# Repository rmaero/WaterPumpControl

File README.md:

Water Pump Controller
Sistema de control automático para bombas de agua en instalaciones residenciales con cisterna y tanque elevado. Diseñado para optimizar el consumo energético y prevenir funcionamiento en seco de la bomba. La version mas actual del firmware es "MEF_IF_EEPROM".

Video demostracion
https://youtu.be/jwLdcLJ9unM

Sistema en producción implementado desde 2023

Estado: En Producción
Operando continuamente desde 2023 sin fallas en instalación residencial real.
REV. B: corregido invertidos pines Rx y Tx, resistencia pulldown de Q1. Agregado conector J10 para programar bootloader (no implementado todavia).

Problema que Resuelve
En sistemas tradicionales de cisterna + tanque elevado, las bombas funcionan con controles manuales, niveles flotantes o temporizadores simples, lo que genera:

Riesgo de funcionamiento en seco (daño a la bomba) en caso de que un sensor falle.
Desperdicio energético (bomba funcionando innecesariamente)
Falta de monitoreo del estado del sistema

Este controlador automatiza completamente el proceso con lógica inteligente. Brinda testigos luminicos para relevar el estado del tanque y de la cisterna (muy util tambien para verificar si los sensores estan funcionando correctamente en caso de aviso de falla).

Características
Hardware

Diseño de PCB custom con microcontrolador ATmega328.
Sensores de nivel de agua en cisterna y tanque
Relé para control de bomba (220V/15A)
Protección contra funcionamiento en seco
Indicadores LED de estado
Posibilidad de usar la placa como standalone sin microcontrolador integrado, sino conectandolo atraves de pines provistos en el etremo izquierdo. Facilidad para usar un ESP32 por ejemplo.

Firmware

Lógica de histéresis para evitar ciclos cortos
Protección multi-nivel:

Detección de cisterna vacía
Timeout de seguridad

Funcionamiento
Lógica básica:

Sensor detecta nivel bajo en tanque y nivel alto en cisterna → activa bomba
Sensor verifica nivel suficiente en cisterna
Bomba llena tanque hasta nivel alto
Sistema entra en standby hasta próximo ciclo

Proteccion contra funcionamiento en seco:
Por defecto, dado el caso para el que se diseñó este circuito, el tanque tiene una capacidad muy superior a la cisterna y la bomba es capaz de vaciar la cisterna en 2:15 minutos. Por lo cual se implementó un timeout que si a los 3 minutos el sensor de la cisterna no está en bajo, asume que es por falla del sensor, apaga la bomba y se queda en estado de ERROR con led rojo parpadeando

Funcion LEARN:
se puede programar que el sistema aprenda de forma automatica cuanto tiempo demora en vaciarse la cisterna. Para esto se debe tener el tanque completamente vacio y la cisterna completamente llena. Con la placa desenergizada, mantener apretado el pulsador "LEARN" y energizar la placa. Una vez que se haya encendido la bomba se puede soltar el pulsador. En este estado el microcontrolador contará el tiempo que demore en vaciarse la cisterna y lo guardará en memoria no volatil (por lo que se puede reiniciar o apagar sin problemas, el tiempo queda guardado). Asi podremos usar la proteccion contra funcionamiento en seco de forma adecuada sin necesidad de cronometrar y reprogramar el micrcocontrolador.

Especificaciones Técnicas

Microcontrolador      ATmega328
Sensores              Tipo: flotantes
Relé                  220V 15A
Alimentación          12V DC 1A
PCB                   2 capas. Dimensiones: 100mm x 80mm. 

Galería
PCB Diseñado

Instalación Real

Requisitos de Hardware

Fuente de alimentación 12V 1A
Sensores de nivel tipo flotante de 3 cables.
Cableado eléctrico certificado para bomba.

Instalación

Montar sensores en cisterna y tanque. Ajustar niveles de la misma forma que en un sistema normal.
Conectar los 3 cables de cada sensor a su correspondiente borne en la PCB.
Verificar alimentando la PCB que las luces testigo esten correctas simulando sobre los sensores manualmente que esta "lleno" o "vacio".
Conectar bomba al relé del controlador.
Alimentar el sistema.
De ser necesario, realizar la rutina de entrenamiento LEARN para calcular y calibrar el tiempo de vaciado de la cisterna.

Resultados en Producción
Desde Marzo 2023:

-Cero fallas de hardware
-Cero activaciones de funcionamiento en seco

Desarrollo Futuro (Versión Comercial)
Mejoras planificadas para siguiente versión de producto:

 Conectividad WiFi para monitoreo remoto
 App móvil para visualización de estado
 Data logging de consumo y ciclos
 Múltiples perfiles de configuración
 Carcasa plástica para montaje industrial
 Certificación eléctrica

 Consideraciones de Seguridad
⚠️ ADVERTENCIA: Este sistema maneja voltaje de red (220V). 

La instalación debe ser realizada por electricista 
Cumplir normativa eléctrica local
Incluir protección térmica en línea de bomba

Licencia
GPL V3

✉️ Contacto
Rodrigo Maero - r.maero@gmail.com
Proyecto personal desarrollado en Rosario, Argentina.

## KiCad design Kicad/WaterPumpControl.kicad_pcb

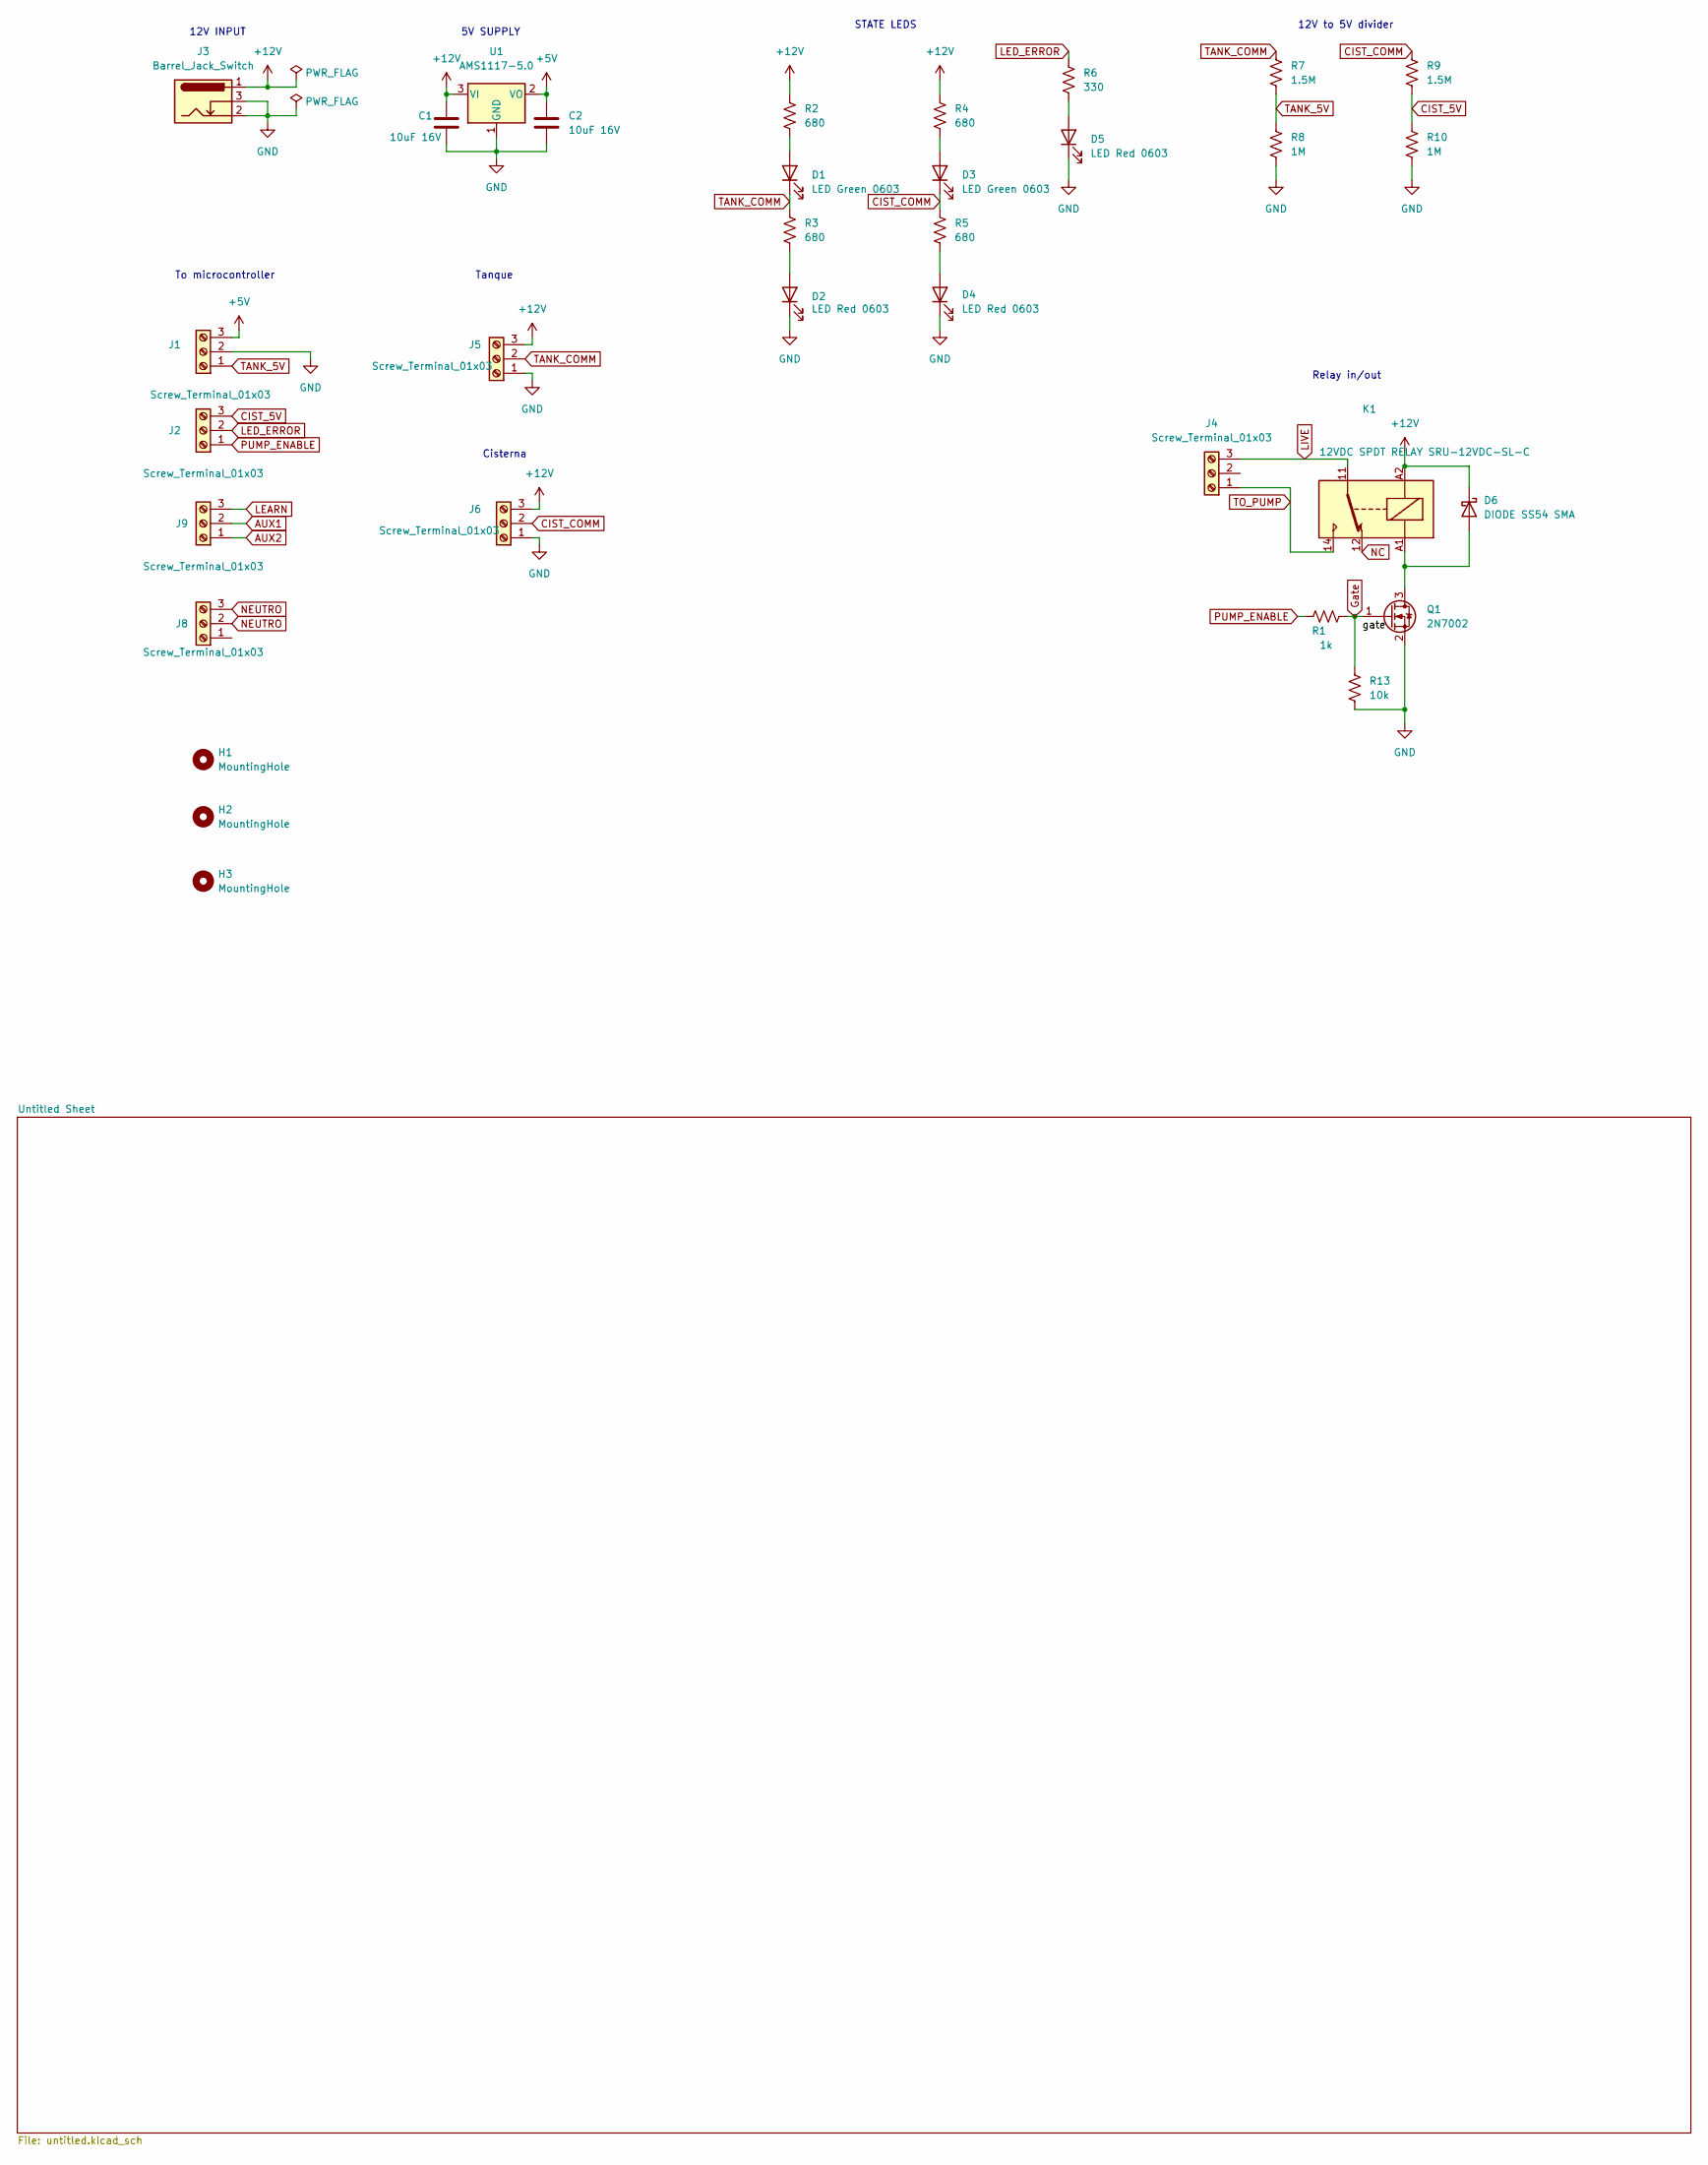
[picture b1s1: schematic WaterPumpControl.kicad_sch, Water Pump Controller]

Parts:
C1, C2: 10uF 16V; C_0603_1608Metric_Pad1.08x0.95mm_HandSolder
D1, D3: LED Green 0603; LED_0603_1608Metric
D2, D4, D5: LED Red 0603; LED_0603_1608Metric
D6: DIODE SS54 SMA; D_SMA
H1, H2, H3: MountingHole; MountingHole_3.2mm_M3
J1, J2, J4, J5, J6, J8, J9: Screw_Terminal_01x03; TerminalBlock_bornier-3_P5.08mm
J3: Barrel_Jack_Switch; BarrelJack_Kycon_KLDX-0202-xC_Horizontal
K1: 12VDC SPDT RELAY SRU-12VDC-SL-C; Relay_SPDT_Finder_36.11
Q1: 2N7002; SOT-23
R1: 1k; R_0603_1608Metric
R2, R3, R4, R5: 680; R_0603_1608Metric
R6: 330; R_0603_1608Metric
R7, R9: 1.5M; R_0603_1608Metric
R8, R10: 1M; R_0603_1608Metric
R13: 10k; R_0603_1608Metric
U1: AMS1117-5.0; SOT-223-3_TabPin2

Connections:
+12V: C1.1, D6.1 (K), J3.1, J5.3, J6.3, K1.A2, R2.1, R4.1, U1.3 (VI)
AUX1: J9.2; also elsewhere on the board
AUX2: J9.1; also elsewhere on the board
CIST_5V: J2.3, R9.2, R10.1; also elsewhere on the board
CIST_COMM: D3.1 (K), J6.2, R5.1, R9.1
GND: C1.2, C2.2, D2.1 (K), D4.1 (K), D5.1 (K), J1.2, J3.2, J3.3, J5.1, J6.1, Q1.2 (S), R8.2, R10.2, R13.2, U1.1 (GND); also elsewhere on the board
Gate: Q1.1 (G), R1.2, R13.1
LEARN: J9.3; also elsewhere on the board
LED_ERROR: J2.2, R6.1; also elsewhere on the board
LIVE: J4.3, K1.11
NC: K1.12
NEUTRO: J8.2, J8.3
unnamed: D1.2 (A), R2.2
unnamed: D2.2 (A), R3.2
unnamed: D3.2 (A), R4.2
unnamed: D4.2 (A), R5.2
unnamed: D5.2 (A), R6.2
unnamed: D6.2 (A), K1.A1, Q1.3 (D)
PUMP_ENABLE: J2.1, R1.1; also elsewhere on the board
TANK_5V: J1.1, R7.2, R8.1; also elsewhere on the board
TANK_COMM: D1.1 (K), J5.2, R3.1, R7.1
TO_PUMP: J4.1, K1.14
VCC: C2.1, J1.3, U1.2 (VO); also elsewhere on the board

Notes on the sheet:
Relay in/out
Cisterna
To microcontroller
Tanque
12V INPUT
12V to 5V divider
5V SUPPLY
STATE LEDS

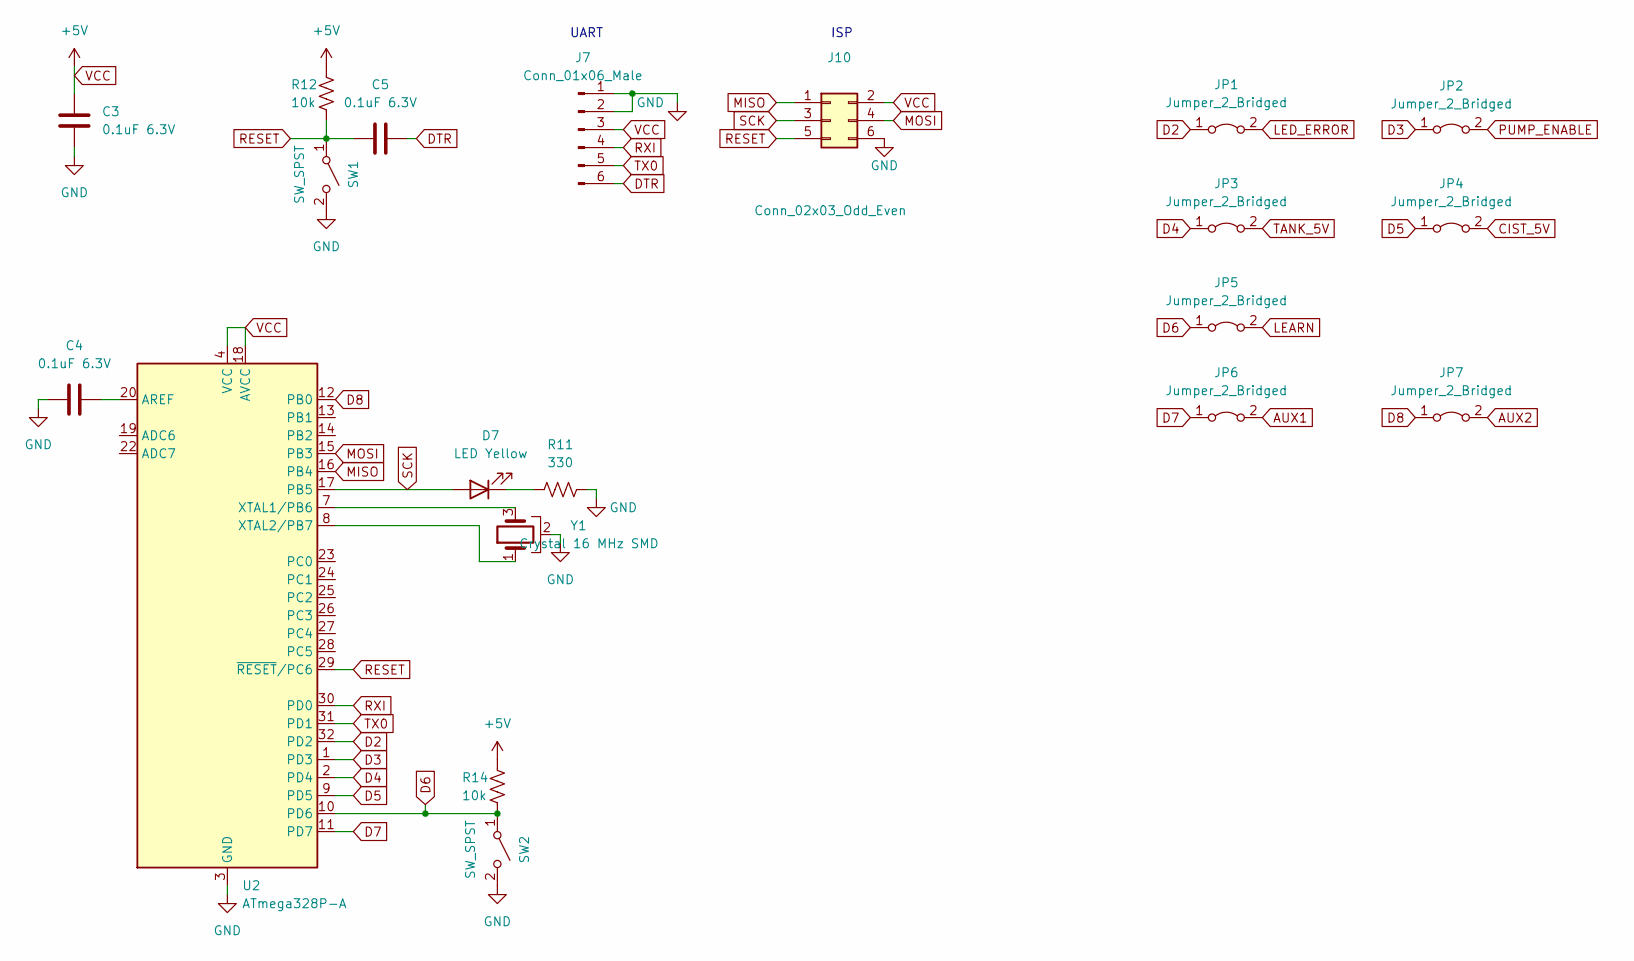
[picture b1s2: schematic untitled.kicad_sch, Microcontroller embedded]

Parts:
C3, C4, C5: 0.1uF 6.3V; C_0603_1608Metric_Pad1.08x0.95mm_HandSolder
D7: LED Yellow; LED_0603_1608Metric
J7: Conn_01x06_Male; PinSocket_1x06_P2.54mm_Vertical
J10: Conn_02x03_Odd_Even; PinHeader_2x03_P2.54mm_Vertical
JP1, JP2, JP3, JP4, JP5, JP6, JP7: Jumper_2_Bridged; SolderJumper-2_P1.3mm_Bridged2Bar_RoundedPad1.0x1.5mm
R11: 330; R_0603_1608Metric
R12, R14: 10k; R_0603_1608Metric
SW1, SW2: SW_SPST; SW_SPST_TL3342
U2: ATmega328P-A; TQFP-32_7x7mm_P0.8mm
Y1: Crystal 16 MHz SMD; Resonator_SMD_Murata_CSTxExxV-3Pin_3.0x1.1mm_HandSoldering

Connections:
AUX1: JP6.2 (B); also elsewhere on the board
AUX2: JP7.2 (B); also elsewhere on the board
CIST_5V: JP4.2 (B); also elsewhere on the board
D2: JP1.1 (A), U2.32 (PD2)
D3: JP2.1 (A), U2.1 (PD3)
D4: JP3.1 (A), U2.2 (PD4)
D5: JP4.1 (A), U2.9 (PD5)
D6: JP5.1 (A), R14.2, SW2.1 (A), U2.10 (PD6)
D7: JP6.1 (A), U2.11 (PD7)
D8: JP7.1 (A), U2.12 (PB0)
DTR: C5.2, J7.6
GND: C3.2, C4.1, J7.1, J7.2, J10.6, R11.2, SW1.2 (B), SW2.2 (B), U2.3 (GND), U2.5 (GND), U2.21 (GND), Y1.2; also elsewhere on the board
LEARN: JP5.2 (B); also elsewhere on the board
LED_ERROR: JP1.2 (B); also elsewhere on the board
MISO: J10.1, U2.16 (PB4)
MOSI: J10.4, U2.15 (PB3)
unnamed: C4.2, U2.20 (AREF)
unnamed: D7.1 (K), R11.1
unnamed: U2.7 (XTAL1/PB6), Y1.3
unnamed: U2.8 (XTAL2/PB7), Y1.1
PUMP_ENABLE: JP2.2 (B); also elsewhere on the board
RESET: C5.1, J10.5, R12.2, SW1.1 (A), U2.29 (~RESET/PC6)
RXI: J7.4, U2.30 (PD0)
SCK: D7.2 (A), J10.3, U2.17 (PB5)
TANK_5V: JP3.2 (B); also elsewhere on the board
TX0: J7.5, U2.31 (PD1)
VCC: C3.1, J7.3, J10.2, R12.1, R14.1, U2.4 (VCC), U2.6 (VCC), U2.18 (AVCC); also elsewhere on the board

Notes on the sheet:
ISP
UART

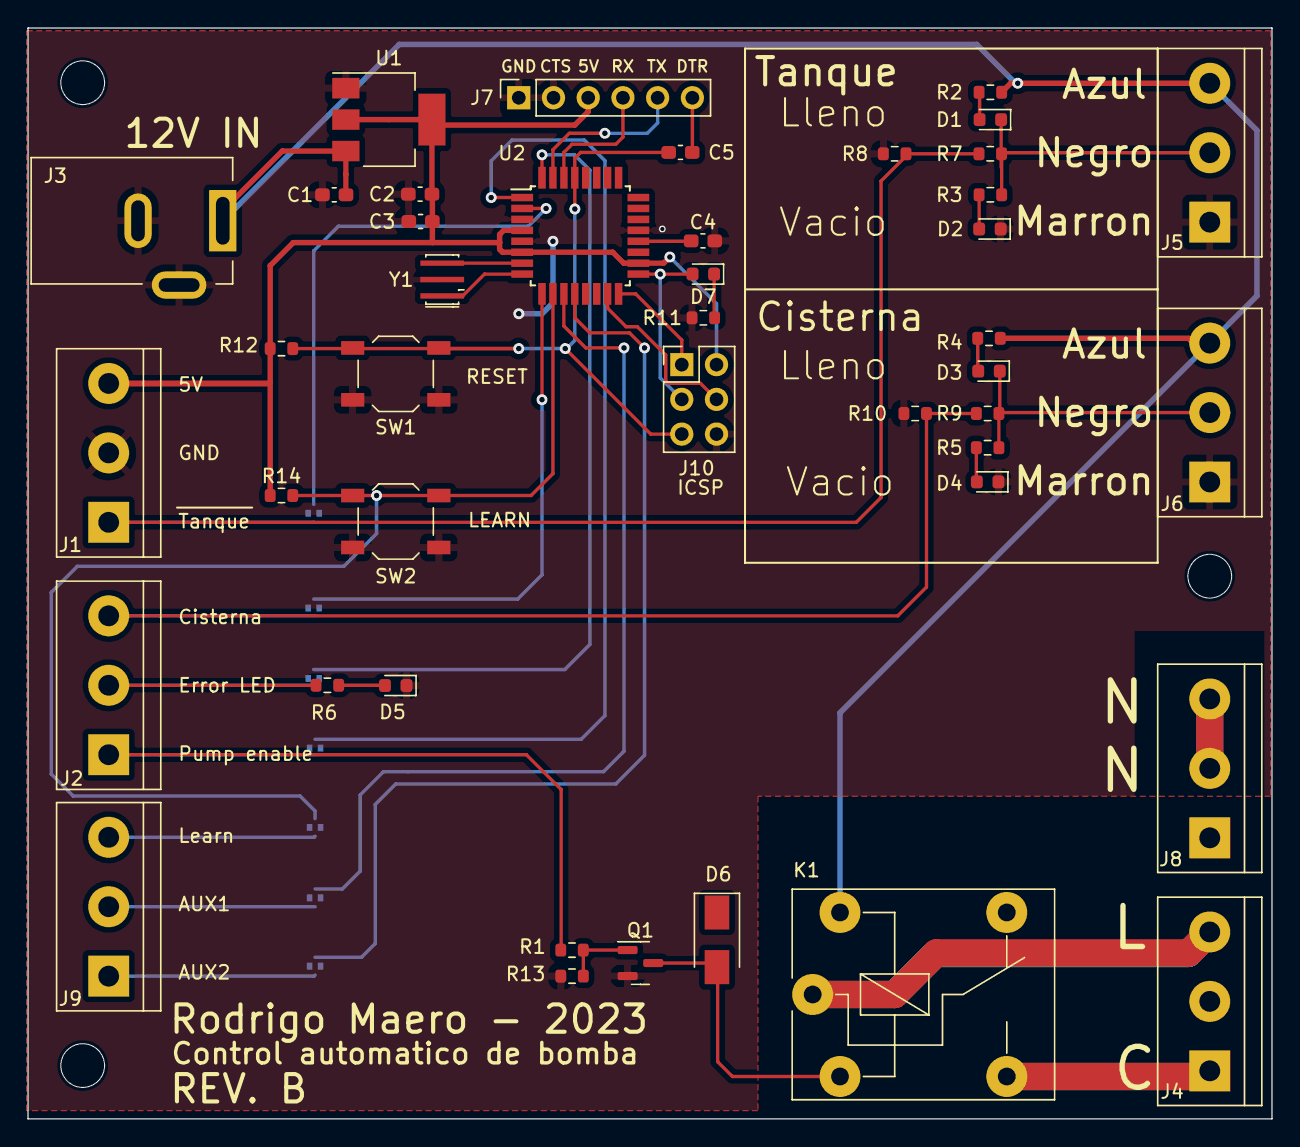
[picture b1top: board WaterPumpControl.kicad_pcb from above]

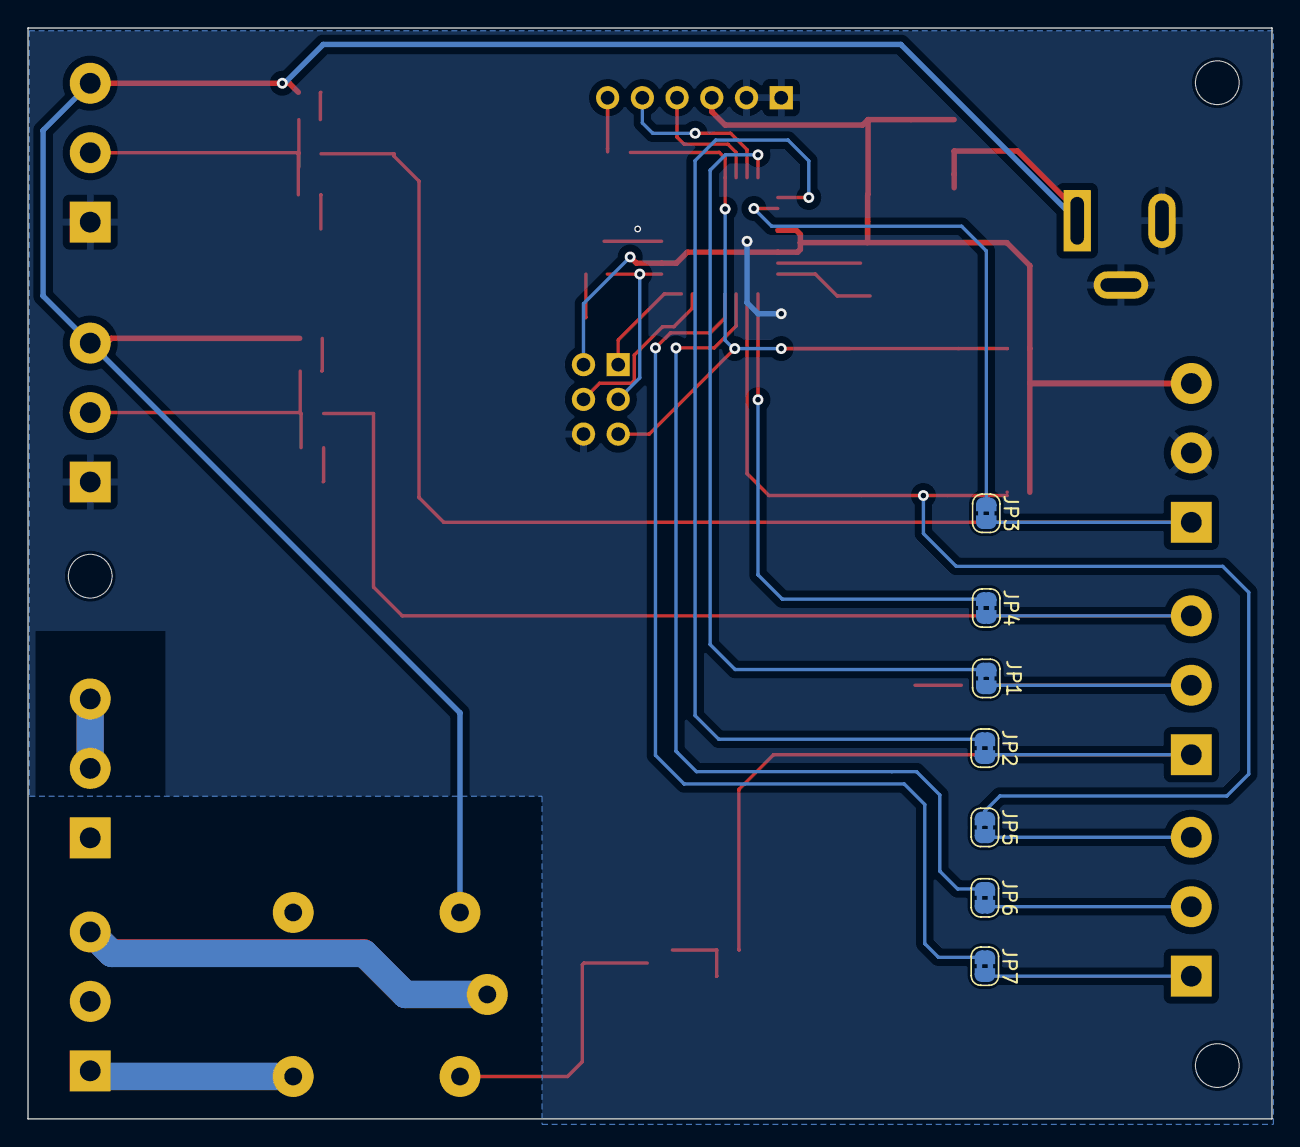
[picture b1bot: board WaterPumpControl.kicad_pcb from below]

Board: 2 copper layers, 91.0 x 79.8 mm, 53 parts (7 on the bottom side), 40 nets.

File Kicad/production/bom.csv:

Designator,Footprint,Quantity,Value,LCSC Part #
C1,0603,1,10uF 16V,
C2,0603,1,10uF 16V,
C3,0603,1,0.1uF 6.3V,
C4,0603,1,0.1uF 6.3V,
C5,0603,1,0.1uF 6.3V,
D1,0603,1,LED Green 0603,
D2,0603,1,LED Red 0603,
D3,0603,1,LED Green 0603,
D4,0603,1,LED Red 0603,
D5,0603,1,LED Red 0603,
D6,D_SMA,1,DIODE SS54 SMA,
D7,0603,1,LED Yellow,
"H1, H2, H3",MountingHole_3.2mm_M3,3,MountingHole,
"J1, J2, J4, J5, J6, J8, J9",TerminalBlock_bornier-3_P5.08mm,7,Screw_Terminal_01x03,
J3,BarrelJack_Kycon_KLDX-0202-xC_Horizontal,1,Barrel_Jack_Switch,
J7,PinSocket_1x06_P2.54mm_Vertical,1,Conn_01x06_Male,
"JP1, JP2, JP3, JP4, JP5, JP6, JP7",SolderJumper-2_P1.3mm_Bridged2Bar_RoundedPad1.0x1.5mm,7,Jumper_2_Bridged,
K1,Relay_SPDT_Finder_36.11,1,12VDC SPDT RELAY SRU-12VDC-SL-C,
Q1,SOT-23,1,2N7002,
R1,0603,1,1k,
R10,0603,1,1M,
R11,0603,1,330,
R12,0603,1,10k,
R13,0603,1,10k,
R14,0603,1,10k,
R2,0603,1,470,
R3,0603,1,470,
R4,0603,1,470,
R5,0603,1,470,
R6,0603,1,330,
R7,0603,1,1.5M,
R8,0603,1,1M,
R9,0603,1,1.5M,
"SW1, SW2",SW_SPST_TL3342,2,SW_SPST,
U1,SOT-223-3_TabPin2,1,AMS1117-5.0,
U2,TQFP-32_7x7mm_P0.8mm,1,ATmega328P-A,
Y1,Resonator_SMD_Murata_CSTxExxV-3Pin_3.0x1.1mm_HandSoldering,1,Crystal 16 MHz SMD,

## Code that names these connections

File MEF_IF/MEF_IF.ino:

#include <EEPROM.h>

#define EEPROM_FLAG_ADDRESS 0
#define EEPROM_TIME_ADDRESS 1

#define PIN_LEARN 6
#define PIN_CISTERNA 5
#define PIN_TANQUE 4
#define PIN_BOMBA 3
#define PIN_LED_ERROR 2
#define AUX1 7
#define AUX2 8
#define TIEMPO_MAX_ON_MILLIS 180000 //3 min *60 seg * 1000 ms = 180.000 millis
#define MIN_TO_MILLIS 60000 // *60 seg * 1000 ms

//debug
#define PIN_LED_INTERNAL 13
bool ledState;

uint32_t maxTimeOn;
uint32_t startLearningTime;
uint32_t startPumpTime;

uint32_t currentTime;
uint32_t shortLoopTime;
uint32_t longLoopTime;


/**************************************************************************
----------------SENSOR INPUTS-----------------------------------------------
***************************************************************************/
//0V = LLENO, 5V=VACIO
bool isCisternaFull()
{
  return  !digitalRead(PIN_CISTERNA);
}

//0V = LLENO, 5V=VACIO
bool isTanqueFull()
{
  return !digitalRead(PIN_TANQUE);
}

/**************************************************************************
----------------RELAY OUTPUT-----------------------------------------------
***************************************************************************/
void turnRelayOn(bool t)
{
  digitalWrite(PIN_BOMBA,t);
//debug led  
  digitalWrite(PIN_LED_INTERNAL,t);
Serial.print("Bomba:");
Serial.println(t);
}


/**************************************************************************
----------------ERROR LED OUTPUT-------------------------------------------
***************************************************************************/
uint16_t ledTimer;
void blinkErrorLed()
{
  if(ledTimer==0)
    {
      ledTimer=1;
      ledState=  !ledState;
    }
  digitalWrite(PIN_LED_ERROR,ledState);

  //DEBUG 
  // digitalWrite(PIN_LED_INTERNAL,ledState);
  Serial.print("Error Led:");
  Serial.println(ledState);

}


/**************************************************************************
----------------MAIN STATE MACHINE-----------------------------------------
***************************************************************************/

typedef enum States {WAITING, LEARNING, PUMP_ON, SM_ERROR};
States relayStateMachine;

void stateMachine()
{
  Serial.print("Estado:");
  Serial.println(relayStateMachine);
//SWITCH-CASE ANDA MAL EN ARDUINO, REEMPLAZO POR IF
  if(relayStateMachine==WAITING)
  {
      if( isCisternaFull()  &&  !isTanqueFull())
      {
        relayStateMachine = PUMP_ON;          
        startPumpTime=millis();        
        turnRelayOn(true);        
      } 
  }else if(relayStateMachine==LEARNING)
  {
      Serial.println("LEARNING");
      turnRelayOn(true);
      if(!isCisternaFull()  ||  isTanqueFull())
      {
        turnRelayOn(false);
        maxTimeOn=millis()-startLearningTime;
        Serial.print("TIEMPO MAX PRENDIDO:");        
        Serial.println(maxTimeOn);
        /*********EEPROM*****************************************************/
        EEPROM.update(EEPROM_FLAG_ADDRESS,1);
        EEPROM.update(EEPROM_TIME_ADDRESS,maxTimeOn/MIN_TO_MILLIS);
        Serial.print("Tiempo max guardado en EEPROM:");        
        Serial.println(EEPROM.read(EEPROM_TIME_ADDRESS));
        /*********EEPROM*****************************************************/
        relayStateMachine = WAITING;
      }
  }else if(relayStateMachine == PUMP_ON)
  { 
      turnRelayOn(true);
      if( !isCisternaFull()  || isTanqueFull()  )
      {
        turnRelayOn(false);
        relayStateMachine = WAITING;
      }
      unsigned long elapsedTime = millis()-startPumpTime;
      
      Serial.print("Quedan ");
      Serial.print((maxTimeOn-elapsedTime)/1000);
      Serial.println(" segundos hasta error");

      if(elapsedTime >= maxTimeOn)
      {
        Serial.print("Pasaron:"); 
        Serial.print(elapsedTime);                 
        Serial.println("ms"); 
        Serial.println("paso estado a ERROR"); 
        relayStateMachine = SM_ERROR;   
        ledTimer=1;      
        turnRelayOn(false);
      }
  }else if(relayStateMachine==SM_ERROR)
  {   
      Serial.println("ERROR"); 
      blinkErrorLed();
  }else{
      relayStateMachine=WAITING;
  }
}


/**************************************************************************
--------------------------------INIT---------------------------------------
***************************************************************************/
void setup() {

//debug 
  pinMode(PIN_LED_INTERNAL, OUTPUT);
  Serial.begin(9600);
  
// BOTON LEARN
  pinMode(PIN_LEARN, INPUT_PULLUP);
  
//SENSORES CISTERNA Y TANQUE //DEBUG WITH BUTTONS: PULLUP
  pinMode(PIN_TANQUE, INPUT);
  pinMode(PIN_CISTERNA, INPUT);

//PINES SALIDA LED Y BOMBA  
  pinMode(PIN_LED_ERROR, OUTPUT);
  pinMode(PIN_BOMBA, OUTPUT);


//SET INITIAL STATE 
  if(digitalRead(PIN_LEARN)==0) //si boton LEARN presionado durante el inicio
  {
    delay(1000);
    if(digitalRead(PIN_LEARN)==0 ) //si sigue presionado 1 seg despues
    {
      if( !isTanqueFull() && isCisternaFull()){ //si esta en el estado correcto (cist llena, tanque vacio)
        relayStateMachine=LEARNING;
      }else{
        relayStateMachine=ERROR;
      }
    }
  }else{
    relayStateMachine=WAITING;
    if(EEPROM.read(EEPROM_FLAG_ADDRESS))
    {
      maxTimeOn = EEPROM.read(EEPROM_TIME_ADDRESS) * MIN_TO_MILLIS ;
      Serial.print("Tomo tiempo guardado en EEPROM (ms):");
      Serial.println(maxTimeOn);
    }else{
      Serial.println("Tomo tiempo default");
      maxTimeOn = TIEMPO_MAX_ON_MILLIS; 
    }
  }
  
  ledTimer=1;
  ledState=0;
  longLoopTime =millis();  
  shortLoopTime=millis();
}

/**************************************************************************
--------------------------------MAIN LOOP----------------------------------
***************************************************************************/
void loop() {
  currentTime = millis();  
  stateMachine();
  /*every 50ms
  if( (currentTime-shortLoopTime) >=50 )
  {
    shortLoopTime = currentTime;
    
  }
  */
  //every 1000ms 
  if( (currentTime-longLoopTime) >=1000)  
  {
    longLoopTime = currentTime;
    if(ledTimer)
    {
      ledTimer--;
    }
  }
}

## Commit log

2023-03-30 Commit inicial. MEF_IF uses if-else instead of switch-case
2023-03-30 Finished READ/WRITE to EEPROM. Needs testing.
2023-03-30 Rutina para guardar en FLASH corregida. Limpieza de mensajes de puerto serie para debug
2026-01-19 Commit inicial de proyecto kicad. Rev B. corregidos pines RX y TX, corregido resistencia pulldown de Q1. Agregado puerto de programacion ICSP para grabar bootloader (no testeado).
2026-01-22 Changed bottom plane from 12V to GND. Added silkscreen for ICSP.
